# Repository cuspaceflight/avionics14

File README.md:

# CUSF Avionics 2014

## Firmware Compilation

Designed to be compiled with the GNU ARM Toolchain - https://launchpad.net/gcc-arm-embedded

The project should simply compile with

    make

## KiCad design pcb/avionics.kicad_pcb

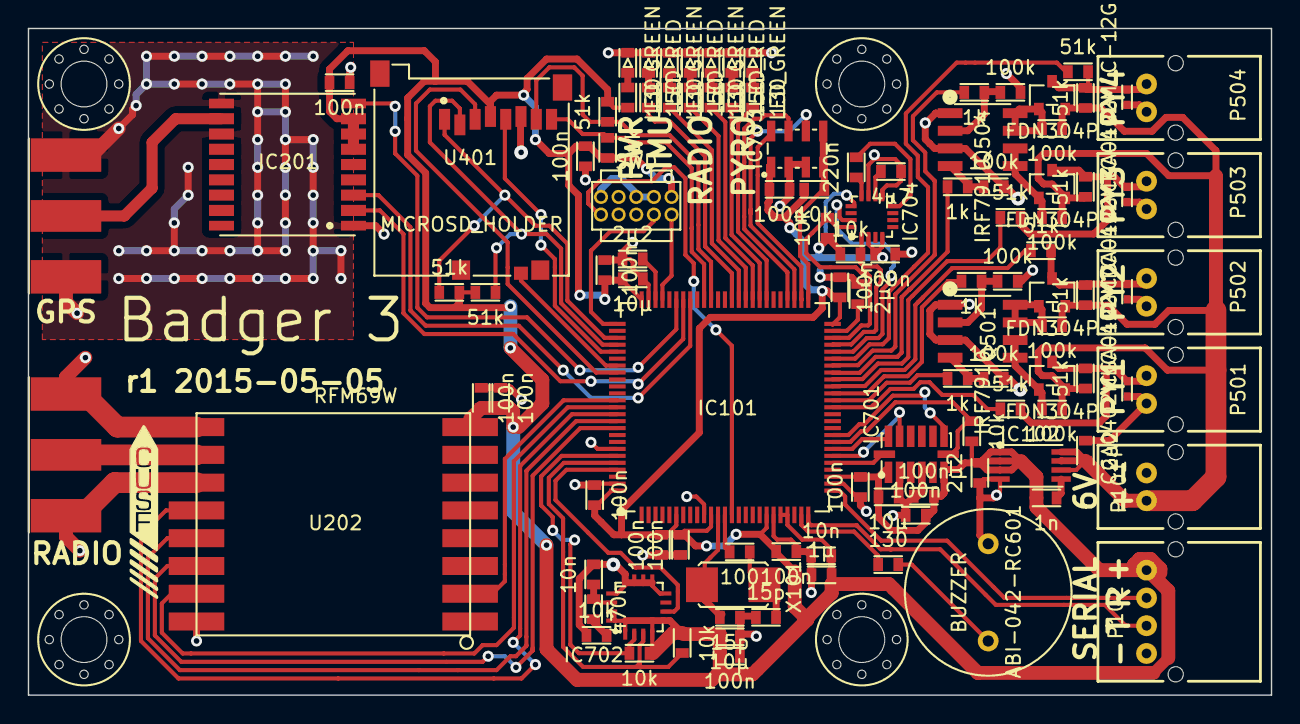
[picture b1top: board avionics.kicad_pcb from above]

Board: 2 copper layers, 89.5 x 48.0 mm, 113 parts (0 on the bottom side), 86 nets.

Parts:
ABI-042-RC601: BUZZER; ABI-042-RC
C101, C701, C702: 10µ; 0603
C102, C103, C105, C109, C110, C112, C114, C201, C203, C204, C401, C703, C704, C705, C708, C709: 100n; 0603
C104: 1µ; 0603
C106, C107: 15p; 0603
C108, C706: 10n; 0603
C111, C113, C115, C117: 2µ2; 0603
C116: 1n; 0603
C707: 470n; 0603
C710: 4µ7; 0603
C711: 220n; 0603
D501, D502, D503, D504: CGA0402MLC-12G; R0402
D601, D603, D605, D607: LED_GREEN; 0603_LED
D602, D604, D606: LED_RED; 0603_LED
IC101: STM32F405VGT; LQFP100
IC102: ADP3335; MSOP8
IC201: MAX-7Q
IC701: ADXL345; ADXL3x5
IC702: L3G4200D
IC703: MS5611-01BA03; MS5611-01BA
IC704: HMC5883L
M3_MOUNT, M3_MOUNT#2, M3_MOUNT#3, M3_MOUNT#4: VAL**; M3_MOUNT
P101, P501, P502, P503, P504: CONN_01X02; S02B-PASK-2
P102: CONN_01X04; S04B-PASK-2
P103: SWD; FTSH-105-01-F-D-K
P201, P202: SMA; SMA-142-0701-801
Q501, Q504: IRF7910; SO-8
Q502, Q503, Q505, Q506: FDN304P; SOT23
R101: 100; 0603
R401, R402, R403, R404, R507, R508, R509, R510, R517, R518, R519, R520: 51k; 0603
R501, R502, R511, R512: 1k; 0603
R503, R504, R505, R506, R513, R514, R515, R516: 100k; 0603
R601, R603, R605, R607, R608: 130; 0603
R602, R604, R606: 150; 0603
R701, R702, R703, R704, R705, R706, R707: 10k; 0603
U202: RFM69W; rfm69w
U401: MICROSD_HOLDER; MEM2051
X101: 8M; XTAL50x32

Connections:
+3V3: C101.1, C102.1, C103.1, C104.1, C105.1, C108.1, C109.1, C110.1, C112.1, C114.1, C116.1, C117.1, C201.1, C203.1, C204.1, C401.1, C701.1, C702.1, C703.1, C704.1, C705.1, C708.1, C709.1, IC101.6, IC101.11, IC101.19, IC101.21, IC101.22, IC101.28, IC101.50, IC101.75, IC101.100, IC102.1, IC102.2, IC102.3, IC201.6, IC201.7, IC201.8, IC701.1, IC701.6, IC702.1, IC702.4, IC702.5, IC702.15, IC702.16, IC703.1, IC704.2, IC704.4, IC704.13, P102.1, P103.1, R401.1, R402.1, R403.1, R404.1, R607.1, R701.2, R702.2, R703.1, R705.2, R706.1, R707.2, U202.8, U401.4
+BATT: C115.1, IC102.6, IC102.7, IC102.8, P101.2, Q502.2, Q503.2, Q505.2, Q506.2, R505.2, R506.2, R507.2, R508.2, R515.2, R516.2, R517.2, R518.2
/Datalogging & Pyros/BUZZER: IC101.24, R608.2
/Datalogging & Pyros/IMU_OK: IC101.61, R603.1
/Datalogging & Pyros/PY1_TRG: IC101.39, R501.1
/Datalogging & Pyros/PY2_TRG: IC101.40, R511.1
/Datalogging & Pyros/PY3_TRG: IC101.43, R502.1
/Datalogging & Pyros/PY4_TRG: IC101.44, R512.1
/Datalogging & Pyros/PY_OK: IC101.57, R601.1
/Datalogging & Pyros/RADIO_OK: IC101.59, R605.1
/Datalogging & Pyros/~IMU_OK: IC101.62, R604.1
/Datalogging & Pyros/~PY1_CHK: IC101.38, R509.2
/Datalogging & Pyros/~PY2_CHK: IC101.41, R519.2
/Datalogging & Pyros/~PY3_CHK: IC101.42, R510.2
/Datalogging & Pyros/~PY4_CHK: IC101.45, R520.2
/Datalogging & Pyros/~PY_OK: IC101.58, R602.1
/Datalogging & Pyros/~RADIO_OK: IC101.60, R606.1
/Datalogging & Pyros/µSD_CD: IC101.82, U401.9
/Datalogging & Pyros/µSD_CLK: IC101.80, U401.5
/Datalogging & Pyros/µSD_CMD: IC101.83, U401.3
/Datalogging & Pyros/µSD_DAT0: IC101.65, R401.2, U401.7
/Datalogging & Pyros/µSD_DAT1: IC101.66, R402.2, U401.8
/Datalogging & Pyros/µSD_DAT2: IC101.78, R403.2, U401.1
/Datalogging & Pyros/µSD_DAT3: IC101.79, R404.2, U401.2
/EXT_RX: IC101.26, P102.2
/EXT_TX: IC101.25, P102.3
/Inertial Measurement/ACCEL_CS: IC101.33, IC701.7, R703.2
/Inertial Measurement/ACCEL_INT: IC101.34, IC701.8
/Inertial Measurement/ACCEL_MISO: IC101.31, IC701.12
/Inertial Measurement/ACCEL_MOSI: IC101.32, IC701.13
/Inertial Measurement/ACCEL_SCK: IC101.30, IC701.14
/Inertial Measurement/BARO_CS: IC101.51, IC703.4, IC703.5, R706.2
/Inertial Measurement/BARO_MISO: IC101.53, IC703.6
/Inertial Measurement/BARO_MOSI: IC101.54, IC703.7
/Inertial Measurement/BARO_SCK: IC101.52, IC703.8
/Inertial Measurement/GYRO_DRDY: IC101.97, IC702.6
/Inertial Measurement/GYRO_SCL: IC101.95, IC702.2, R701.1
/Inertial Measurement/GYRO_SDA: IC101.96, IC702.3, R702.1
/Inertial Measurement/MAGNO_DRDY: IC101.46, IC704.15
/Inertial Measurement/MAGNO_SCL: IC101.47, IC704.1, R705.1
/Inertial Measurement/MAGNO_SDA: IC101.48, IC704.16, R707.1
/Radio/GPS_nRST: IC101.70, IC201.9
/Radio/RADIO_CLK: IC101.89, U202.12
/Radio/RADIO_CS: IC101.88, U202.15
/Radio/RADIO_IRQ: IC101.87, U202.2
/Radio/RADIO_MISO: IC101.90, U202.13
/Radio/RADIO_MOSI: IC101.91, U202.14
/Radio/RX: IC101.68, IC201.3
/Radio/TX: IC101.69, IC201.2
/SWDCLK: IC101.76, P103.4
/SWDIO: IC101.72, P103.2
/nReset: IC101.14, P103.10
GND: ABI-042-RC601.2, C101.2, C102.2, C103.2, C104.2, C105.2, C106.2, C107.2, C108.2, C109.2, C110.2, C111.2, C112.2, C113.2, C114.2, C115.2, C117.2, C201.2, C203.2, C204.2, C401.2, C701.2, C702.2, C703.2, C704.2, C705.2, C706.1, C708.2, C709.2, C710.2, D501.2, D502.2, D503.2, D504.2, D601.2, D602.2, D603.2, D604.2, D605.2, D606.2, D607.2, IC101.10, IC101.20, IC101.27, IC101.74, IC101.94, IC101.99, IC102.4, IC201.1, IC201.10, IC201.12, IC701.2, IC701.4, IC701.5, IC702.8, IC702.9, IC702.10, IC702.11, IC702.12, IC702.13, IC703.2, IC703.3, IC704.9, IC704.11, P101.1, P102.4, P103.3, P103.5, P103.9, P201.2, P201.3, P201.4, P201.5, P202.2, P202.3, P202.4, P202.5, P501.2, P502.2, P503.2, P504.2, Q501.1, Q501.3, Q504.1, Q504.3, R503.1, R504.1, R513.1, R514.1, R704.2, U202.9, U202.11, U202.16, U401.6
unnamed: ABI-042-RC601.1, R608.1
unnamed: C106.1, IC101.12, X101.1
unnamed: C107.1, R101.2, X101.2
unnamed: C111.1, IC101.49
unnamed: C113.1, IC101.73
unnamed: C116.2, IC102.5
unnamed: C706.2, C707.2, IC702.14
unnamed: C707.1, R704.1
unnamed: C710.1, IC704.10
unnamed: C711.1, IC704.8
unnamed: C711.2, IC704.12
unnamed: D501.1, P501.1, Q502.3, R507.1, R509.1
unnamed: D502.1, P502.1, Q505.3, R517.1, R519.1
unnamed: D503.1, P503.1, Q503.3, R508.1, R510.1
unnamed: D504.1, P504.1, Q506.3, R518.1, R520.1
unnamed: D601.1, R601.2
unnamed: D602.1, R602.2
unnamed: D603.1, R603.2
unnamed: D604.1, R604.2
unnamed: D605.1, R605.2
unnamed: D606.1, R606.2
unnamed: D607.1, R607.2
unnamed: IC101.13, R101.1
unnamed: IC201.11, P201.1
unnamed: P202.1, U202.10
unnamed: Q501.2, R511.2, R513.2
unnamed: Q501.4, R501.2, R503.2
unnamed: Q501.5, Q501.6, Q502.1, R505.1
unnamed: Q501.7, Q501.8, Q505.1, R515.1
unnamed: Q503.1, Q504.5, Q504.6, R506.1
unnamed: Q504.2, R512.2, R514.2
unnamed: Q504.4, R502.2, R504.2
unnamed: Q504.7, Q504.8, Q506.1, R516.1

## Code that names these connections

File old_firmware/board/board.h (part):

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 * PB0  - PIN0                      (input pullup).
 * PB1  - PIN1                      (input pullup).
 * PB2  - PIN2                      (input pullup).
 * PB3  - BARO_SCK                  (alternate 6).
 * PB4  - BARO_MISO                 (alternate 6).
 * PB5  - BARO_MOSI                 (alternate 6).
 * PB6  - SER_OUT_1                 (alternate 7).
 * PB7  - SER_IN_1                  (alternate 7).
 * PB8  - MAGNO_SCL                 (alternate 4).
 * PB9  - MAGNO_SDA                 (alternate 4).
 * PB10 - GYRO_SCL                  (alternate 4).
 * PB11 - GYRO_SDA                  (alternate 4).
 * PB12 - LG_ACCEL_CS               (output pushpull).
 * PB13 - LG_ACCEL_SCK              (alternate 5).
 * PB14 - LG_ACCEL_MISO             (alternate 5).
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 * PD4  - PIN4                      (input pullup).
 * PD5  - SER_OUT_2                 (alternate 7).
 * PD6  - SER_IN_2                  (alternate 7).
 * PD7  - BARO_CS                   (output pushpull).
 * PD8  - LG_ACCEL_INT2             (input pullup).
 * PD9  - LG_ACCEL_INT1             (input pullup).
 * PD10 - LG_ACCEL_CS               (input pullup, pin driven by PB12).
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/*
 * GPIOE setup:
 *
 * PE0  - MAGNO_DRDY                (input pullup).
 * PE1  - PIN1                      (input pullup).
 * PE2  - PIN2                      (input pullup).
 * PE3  - PIN3                      (input pullup).
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 * PE11 - PYRO_2_F                  (output pushpull).
 * PE12 - PYRO_3_F                  (output pushpull).
 * PE13 - GYRO_INT1                 (input pullup).
 * PE14 - GYRO_DRDY                 (input pullup).
 * PE15 - PIN15                     (input pullup).
 */
#define VAL_GPIOE_MODER             (PIN_MODE_INPUT(GPIOE_MAGNO_DRDY)       |\
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
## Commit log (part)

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2014-11-03 Add test file.
2014-11-03 branch commit
2014-11-06 Added GPS module
2014-11-06 Added a2235-h.lib
2014-11-06 Added minimimum spesifications
2014-11-06 GPS module
    Finished the GPS module and labeled the inputs/putputs
2014-11-07 Setup up barebones ChibiOS project and added details to README.md on how to compile it.
    The configuration files are copied from Martlet 2 and so will likely need modification once the PCB design has been finalized.
2014-11-08 Created 3D translational kalman filter written in C that should easily be ported over to the STM32.
    I decided against using a matrix library as it seemed very wasteful given that most of the matrices were mainly 0s (the state transition matrix had 61). Instead I opted to handle the axes completely 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
    The barometer calibration was copied from the Martlet 2 repo as I didn't see any benefit to rewriting it. The covariance update was also copied as doing it again by hand seemed like a waste of time.
2014-11-11 Added header files
2014-11-14 microsd: added initial files with todos.
2014-11-14 datalogging: added initial files with todos.
2014-11-14 config: aaand, fixed the first bug
2014-11-14 fixed state transition order
2014-11-15 MATLAB implementation of the QUEST algorithm for estimating the state quaternion based on accelerometer and magnetometer data which will then be fed into the orientation kalman filter. It works as fa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
2014-11-16 add rf module to schematic
2014-11-16 Update mission_control_bottom.c
    Was missing states, so fixed this
    Bottom is now in control of firing the separation e-match
2014-11-16 Create pyro.c
    More of a template for the pyrotechnics driver
2014-11-16 microsd: clarified some decisions in the interface provided by microsd.
2014-11-19 Added continuity checks, fixed bugs
2014-11-19 Missing resistor library component added. (Resistors are not square boxes!)
2014-11-25 datalogging: now all sd and no ff!!!
2014-11-25 microsd: added the basic file system access functions.
2014-11-25 config: added cleanup.
2014-11-26 config: this is more clear (and more correct)
2014-11-26 Added in uSD hardware. I'm assuming we're using SPI, if not the pins have to be connected differently. uSD card holder is the MEM2051 in farnell. Not entirely sure about pullup resistors, and whether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
2014-11-28 config: now with basic test, wow.
    also changed signature of config_init (now accepts path to config
    as parameter).
    added basic check of whether the file is non-negative.
2014-11-28 antenna connector symbol
2014-11-28 Resolved issues with Pyro Schematics + a little tidying up. - PMOS upside down - TVS diode for ESD (ESD8V0R1B-02LS at 2.18p each, 1.91p each (25-99), 1.72p each (100-249)) - Replaced Heirachial Pins 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
2014-11-28 Rectified microSD Card Hardware. - 51k pullups - SDIO configuration - TVSD removed - 100nF cap
2014-11-29 Changed indicators to single pin single LED on advice. - Ran ERC and solved the large errors.
2015-01-09 Created a simple GUI for processing and viewing flight data in 3D.
    It currently accepts data in the Martlet 2 telemetry format and uses the sensor data to test out the state estimation algorithms (currently attitude is not calculated). It then renders this in 3D in 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
    The project is split into two main projects, Avionics and Avionics.GUI, the former being a C library containing code that should be easily ported to run on the STM32 and the latter containing all the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
    Avionics.GUI has a few depen
2015-01-17 add rfm69, changed gps schematic
2015-01-23 Added buzzer to schematic to allow one more form of error reporting.
2015-01-25 Added test root widget for ground station
2015-02-03 removed old groundstation
2015-02-05 footprint files
2015-02-07 Created black box state estimator to accept raw data and handle calling the individual state estimators
    Fixed some problems with the Quest Algorithms output, some of the sequential rotations were incorrect causing the rotations around certain axis to be inverted
    Added ability to receive real time data over a serial port
    Added calibration MatLab scripts for magnetometers and accelerometers which uses an ellipsoid fitter I found online and a non-linear Gauss newton approach to correct for bias and scaling factors.
2015-02-09 export pins to main sheet, add IMU
2015-02-10 Added covariance estimation to the calibration MatLab scripts. This can then be used by the translation kalman filter. Brief tests have shown this gives much better results than the previous value.
    Added serial packet timestamp synchronization although for some reason this causes the simulation to lag noticeably behind.
    Added a start delimiter of the characters 'SY' to the serial data format.
    The bias values for the accelerometer (computed for the QUEST algorithm) are now subtracted from the accelerometer values before being fed into the kalman filter, as opposed to previously where gravi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
2015-02-10 update schematic after today's meeting
2015-02-13 connect pins to micrcontroller where we decided last meeting
2015-02-13 more schematic work
2015-02-16 register settings: 433MHz, 10dBm, 1200bps
2015-02-16 pin numbers
2015-02-16 pin numbers, circle to indicate pin 1
2015-02-17 footprint assignment
2015-02-18 move sch libraries inside library folder
2015-02-18 swap GPS module to uBlox
2015-02-19 Groundstation update
2015-02-21 add log functions & mempool, removed receive functions (radio only used as transmitter)
2015-02-21 expose log functions to external threads
2015-02-22 fixed variable declaration
2015-02-23 Added labels to bars and made it easier to add and remove new bars.
2015-02-23 Updated groundstation: added simpler parser, test data, update called only when necessary
2015-02-27 Added telemetry data and a version trying to read that. Feel free to ignore that version if it is worth starting over.
2015-03-07 Removed data file
2015-03-07 continue pyro routing
2015-03-08 Tried to route a little more of the board. Are the jumps ok?
2015-03-08 Added logs again
2015-03-09 routing after today's meeting
2015-03-10 Have continued routing the PCB. I have tried to make it more compact on the right side of the PCB. It is still possible to push it more togheter by moving the microcontroller into the gap to its righ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
2015-03-12 I have moved the microcontroller to what I believe is the optumum position. I have also changed the transistor for the buzzer to a 300R resistor and the buzzer pin to pin 24 PA1. I had to reconnect a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
2015-03-12 continued routing, note that we need to solve how to connect nReset and also how to power all the VDDs.
2015-03-12 tidied up some routing
2015-03-12 yet more routing done!
2015-03-13 WE'RE FINALLY DONE!!!
2015-03-14 include config header, driver works when tested on dev board
2015-04-06 I have started a spreadsheet for helping us finish the pcb and order the correct components, please feel free to help me fill it out and check the footprints for the components
2015-04-26 Updated to latest version of Frontier.Engine
2015-04-27 Reworked gyro and magnetometer drivers to be more customizable and support more features. Magnetometer driver is based on the one found at https://github.com/DuinoPilot/trunetcopter and I tried to ma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
    Gyroscope driver doesn't yet perform automatic calibration but I plan to add this shortly.
    Updated ChibiOS to point to a stable branch rather than master (which I had accidentally set it to track).
2015-05-05 I have added the Farnell code to a series of sheets
2015-05-05 Added order numbers for all parts
2015-05-05 Added order codes for missing parts
2015-05-06 add power led, change resistor for buzzer
2015-05-06 100n not 100nF capacitor on uSD.sch
2015-05-06 10k not 10K resistor on imu.sch
2015-05-06 add farnell BOM
2015-05-06 add power LED
2015-05-06 Improve power routing
    * remove long track on far right
    * thicken up main carrier on bottom
    * route GPS through decoupling cap
2015-05-06 increase clearance around gps antenna trace
2015-05-06 remove copper under magno
2015-05-06 tidy up removed copper under magno
2015-05-07 update with new format BOM
2015-05-07 update 2pin header P101 to RS (in-stock) code
2015-05-07 change to in-stock SMA connector
2015-05-22 new firmware
2015-05-22 add a shell
2015-05-22 radio works!
2015-05-24 Added a LED test
2015-05-24 added global variables global_temperature and global_pressure to ms5611.h and their updating lines in ms5611.c. Added a test to b3_shell.c
2015-05-24 added the #include line in b3_shell. Forgot to do so earlier.
2015-05-24 Modified hmc5883l.h and .c to add in global_magnoxyz (a uint16 array size 3) and then b3_shell to have a test.
2015-05-24 Fixed some stuff that I was mistaken about.
2015-05-24 Added in the typecasting just in case.
2015-05-24 Compiled baro, working!
2015-05-25 doesn't work, look at datasheet
2015-05-25 datalogging: bit more consistent microsd-ness (style+clarifying comments).
2015-05-25 fixed bugs in pyro test
2015-05-27 add GPS test and use both UART2 outputs
2015-05-27 radio pin allocations
2015-05-27 radio driver files
2015-05-27 add cmd_radio_tx to map and rfm69 to makefile
2015-05-27 set power amplifier 0 instead of 1
2015-05-27 change SPI functions, led indicators for initialisation
2015-05-27 Tried fixing the magno driver. Current values set for the magno are default. We'll probably want to increase the frequency of fetching, and adjust the gain depending on the magnetic field in the UK.
2015-05-27 radio test probably working
2015-05-27 ive always wanted to use goto
2015-05-28 datalogging: fixed read bug (reset file ptr, may need more flexibility).
    Test should be working ish. Although it still occasionally fails on
    file opening (timeout error + CRC check error). Need to investigate!
2015-05-28 add gps parsing code (not tested yet)
2015-05-28 make board.h as sensible as possible for i2c
2015-05-28 Revert "store this nice working magno test code in a commit"
    This reverts commit 65a51313166a4cd027eda75cebae3e59f1787c54.
2015-05-28 changed pyro shell
2015-05-28 arduino receiver station
2015-05-28 removed thread
2015-05-28 fix arduino include syntax
2015-05-28 more updates to pyro shell
2015-05-28 run radio thread in main, call log function in test
2015-05-28 remove merge conflict marker from main.c
2015-05-28 added a test_all function to shell
2015-05-30 take out rssi
2015-05-30 updated mission control
2015-05-30 integrated mission control into one file
2015-05-30 mission control for single stage
2015-05-30 changes to gyro - works on top board
2015-05-30 further magno/gyro playing
2015-05-30 gyro works yay
2015-05-30 checksum + 2 x syncwords + fixed payload length of 17
2015-05-30 radio works woo
2015-05-30 output the raw int16 from gyros
2015-05-30 Forgot to delete the old file.
2015-05-31 Spotted a small bug in the init function that would make its success checking less effective than it should be.
2015-06-03 chibiOS commit
2015-06-03 add local fatfs so no need to unzip
2015-06-03 fix all build warnings
2015-06-03 add state diagram and telem doc
2015-06-03 start work on combined mission control
2015-06-03 add WAIT_IGNITION state for cases when next stage is ignited by separation charge only
2015-06-04 update config.c/h for new settings
2015-06-04 implement state machine functions and update pyro driver to use new config settings
2015-06-04 add datalogging sending to radio
2015-06-04 also check that no pyros connected if none should be
2015-06-05 add datalogging to things
2015-06-05 Added software for groundsation
2015-06-05 Removed graph and moved bars, added a bager
2015-06-05 add config thread
2015-06-05 enable string funcs in ffconf
2015-06-05 fix out of bounds memory access in hmc
2015-06-05 check for unalloc'd mem in RFM69
2015-06-05 add new threads to main.c
2015-06-05 check in the case drawings
2015-06-05 fix potential sad race condition in accel/gyro driver
2015-06-05 tidy shell threads table formatting
2015-06-05 set config thread name
2015-06-05 enable gyro thread
2015-06-05 fix alt issue if pressure>Pb[0]
2015-06-05 Implemented parser, bars work
2015-06-06 add config control of radio, gyro, magno, gps
2015-06-06 don't dupe trusting baro
2015-06-06 add tweeter code
2015-06-06 add basic mission control testing framework
2015-10-19 set different frequencies based on which stage of the rocket flight computer sits in
2015-10-20 Further file removals - accidentally omitted from 9b26e4cb265dfb7f280c8eaeddb3f6328c037d2e
2015-11-01 changed input amplifiers setting in receiver station
2015-11-01 add first go at simple groundstation python
2015-11-01 add new pad altitude cal msg to telemetry.md
